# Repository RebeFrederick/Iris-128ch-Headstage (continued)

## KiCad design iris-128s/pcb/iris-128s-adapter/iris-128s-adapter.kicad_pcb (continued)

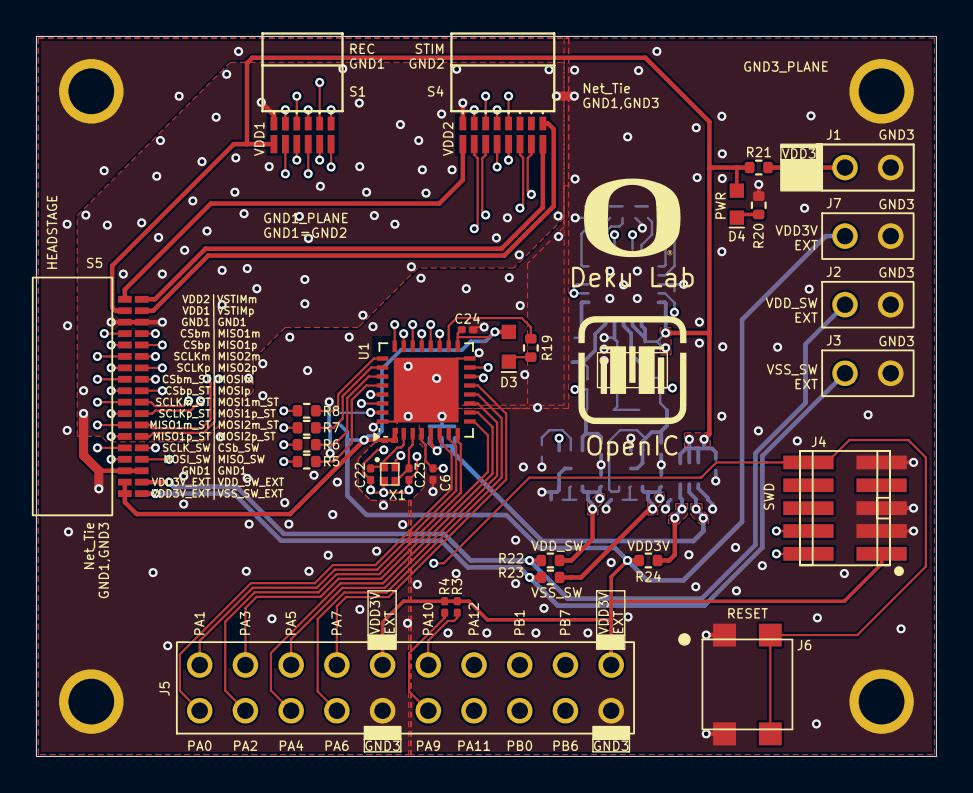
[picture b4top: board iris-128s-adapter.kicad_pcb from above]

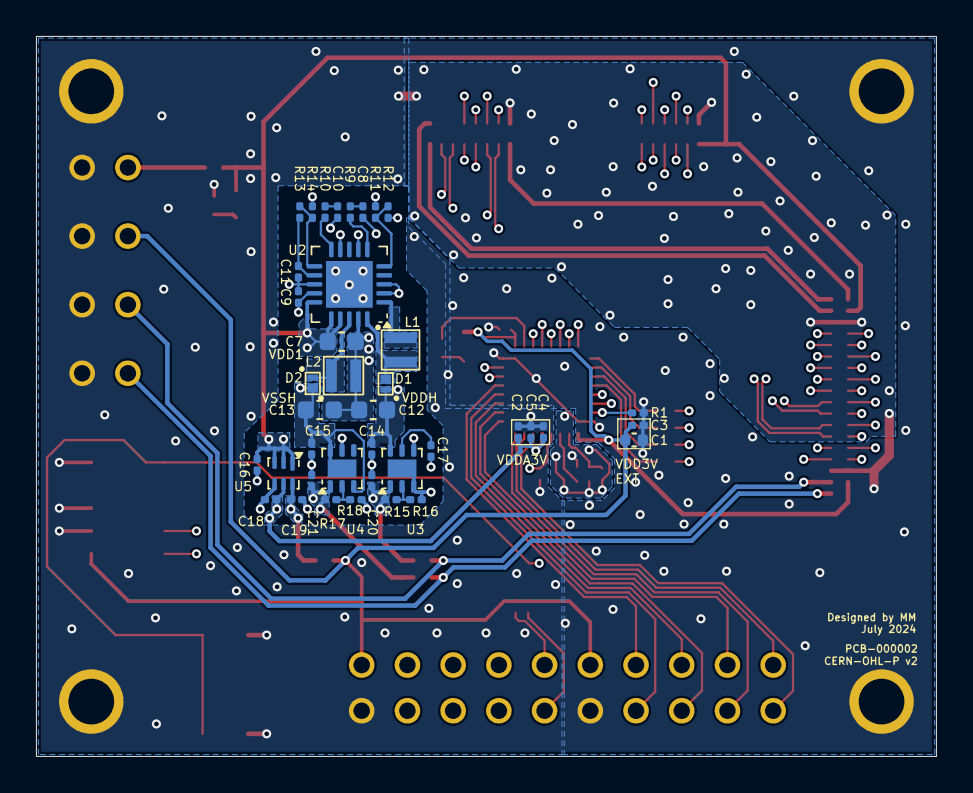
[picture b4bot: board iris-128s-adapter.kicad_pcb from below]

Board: 4 copper layers, 50.0 x 40.0 mm, 75 parts (39 on the bottom side), 83 nets.

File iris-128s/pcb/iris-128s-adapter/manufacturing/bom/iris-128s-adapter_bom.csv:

"Reference","Value","Qty","DNP","MPN","Manufacturer","Description"
"C1","4.7u","1","","KGM05CR51C475MH","Kyocera AVX","Unpolarized capacitor"
"C2,C9,C11,C16,C18,C19","1u","6","","GRM033R61C105ME15D","Murata Electronics","Unpolarized capacitor"
"C3,C4,C6,C24","100n","4","","C0603X5R1C104K030BC","TDK","Unpolarized capacitor"
"C5","10n","1","","GRM033R61C103KA12D","Murata Electronics","Unpolarized capacitor"
"C7,C12,C13","10u","3","","GRM188R61E106KA73D","Murata Electronics","Unpolarized capacitor"
"C8,C10","33n","2","","GRM033R61C333KE84D","Murata Electronics","Unpolarized capacitor"
"C14,C15,C20,C21","2.2u","4","","GRM035R61C225ME01D","Murata Electronics","Unpolarized capacitor"
"C17","1n","1","","GRM033R61E102KA01J ","Murata Electronics","Unpolarized capacitor"
"C22,C23","2p","2","","GJM0335C1E2R0WB01D","Murata Electronics","Unpolarized capacitor"
"D1,D2","~","2","","SDM05U20CSP-7 ","Diodes Incorporated",""
"D3","~","1","","CSL1901UW1","ROHM","LED-RED-0603-ROHM-CSL1901UW1"
"D4","~","1","","LGQ396","OSRAM","LED-GREEN-0603-OSRAM-LGQ396"
"J1,J2,J3,J7","~","4","","TLW-102-06-G-S","Samtec","Header-Low-Profile-Male-2_2x1_P0.1in"
"J4","~","1","","FTSH-105-01-L-DV-K","Samtec","ARM10-10_2x5_P0.05in"
"J5","~","1","","SLW-110-01-G-D","Samtec","Header-Low-Profile-Female-20_2x10_P0.1in"
"J6","~","1","","7914G-1-000","Bournes","PUSHBUTTON-7914G-1-000"
"L1","3.3u","1","","XFL2006-332MEC","Coilcraft",""
"L2","4.7u","1","","XFL2006-472MEC","Coilcraft",""
"R1","0","1","","RC0201FR-070RL","Yageo","Resistor"
"R3,R4","4.7k","2","","RC0201FR-074K7L","Yageo","Resistor"
"R5,R6,R7,R8,R21,R22,R23,R24","0","8","","RC0402JR-070RL","Yageo","Resistor"
"R9","4.87k","1","","RC0201FR-074K87L","Yageo","Resistor"
"R10","7.5k","1","","RC0201FR-077K5L","Yageo","Resistor"
"R11","1.15M","1","","CRCW02011M15FNED","Vishay Dale","Resistor"
"R12,R13","100k","2","","RC0201FR-07100KL","Yageo","Resistor"
"R14","1.33M","1","","CRCW02011M33FNED","Vishay Dale","Resistor"
"R15","8.06k","1","","RC0201FR-078K06L","Yageo","Resistor"
"R16,R18","10k","2","","RC0201FR-0710KL","Yageo","Resistor"
"R17","64.9k","1","","RC0201FR-0764K9L","Yageo","Resistor"
"R19","402","1","","RCS0402402RFKED","Vishay Dale","Resistor"
"R20","499","1","","RCS0402499RFKED","Vishay Dale","Resistor"
"S1","~","1","","A79623-001","Omnetics","12-pin Omnetics connector for RHD2000-Cable-Amp-Side"
"S2,S3,S6,S7","~","4","","None","None","MOUNTING_HOLE-PAD-0.1IN"
"S4","~","1","","A79633-001","Omnetics","16-pin Omnetics Connector for RHD2000"
"S5","~","1","","A79024-001","Omnetics","36-pin Omnetics Connector"
"U1","~","1","","STM32U083KCU6","ST Microelectronics","STM32 Ultra-low-power Arm M0+, 32-bit MCU"
"U2","~","1","","ADP5070ACPZ-R7","Analog Devices","DC-to-DC Switching Regulator with Independent Positive and Negative Outputs"
"U3","~","1","","ADP7142ACPZN5.0-R7","Analog Devices","40 V, 200 mA, Low Noise, CMOS LDO Linear Regulator"
"U4","~","1","","ADP7182ACPZN-R7","Analog Devices","–28 V, −200 mA, Low Noise, Linear Regulator"
"U5","~","1","","TLV7113030DDSER","Texas Instruments","Dual, 200mA, Low-IQ Low-Dropout Regulator for Portable Devices"
"X1","~","1","","  ECS-.327-6-1210B-N-TR","ECS","CRYSTAL-ECS-ECX-1210B-32KHZ"

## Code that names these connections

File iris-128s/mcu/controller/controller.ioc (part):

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Mcu.Name=STM32U083KCUx
Mcu.Package=UFQFPN32
Mcu.UserName=STM32U083KCUx
PA15.Signal=GPIO_Output
PA8.Signal=GPIO_Output
PB3.Mode=Full_Duplex_Master
PB3.Signal=SPI3_SCK
PB4.Mode=Full_Duplex_Master
PB4.Signal=SPI3_MISO
PB5.Mode=Full_Duplex_Master
PB5.Signal=SPI3_MOSI
PC14-OSC32_IN.Signal=RCC_OSC32_IN
PC15-OSC32_OUT.Signal=RCC_OSC32_OUT
RCC.HSE_VALUE=4000000
RCC.SYSCLKFreq_VALUE=16000000
board=custom

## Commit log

2025-08-15 another commit
2025-10-24 Add CERN Open Hardware Licence
    Added CERN Open Hardware Licence Version 2 - Permissive to the project.
2025-10-24 update with pcb and mcu files.
2025-10-24 small update on documentation.
2025-10-24 Create iris-128b
2025-10-24 Added iris-128b.
2025-10-25 added description of the system in README file and a few small changes.
2025-10-25 simplified folder structure table and moved file type table to device-folder.
2025-10-26 Added documentation to the README for iris128b.
2025-10-29 adapter board files
2025-10-29 Thinfilm documentation
2025-10-29 license update, readme, and manufacturing files
2025-10-29 formatting readme
2025-10-29 formatting
2025-10-30 sync commit
2025-10-30 update iris-128s with documentation.
2025-10-30 minor update to NOTICE and README files.
2025-10-30 added link to docs.openic.org
2025-10-31 small doc-site link update.
2025-11-04 added documentation link.
2025-11-04 minor change
2025-11-04 readme files
2025-11-05 documentation folder
2025-11-07 images and documentation
2025-11-13 documentation
2025-11-13 mcudocumentation
2025-11-14 added datasheets of iris_128s.
2025-11-15 datasheets
